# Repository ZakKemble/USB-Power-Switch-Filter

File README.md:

USB Power Switch and Filter
===========================

A simple USB power switch with current limit, soft start, noise filtering and ESD protection.

http://blog.zakkemble.co.uk/usb-power-switch-and-filter/

---

Zak Kemble

contact@zakkemble.co.uk

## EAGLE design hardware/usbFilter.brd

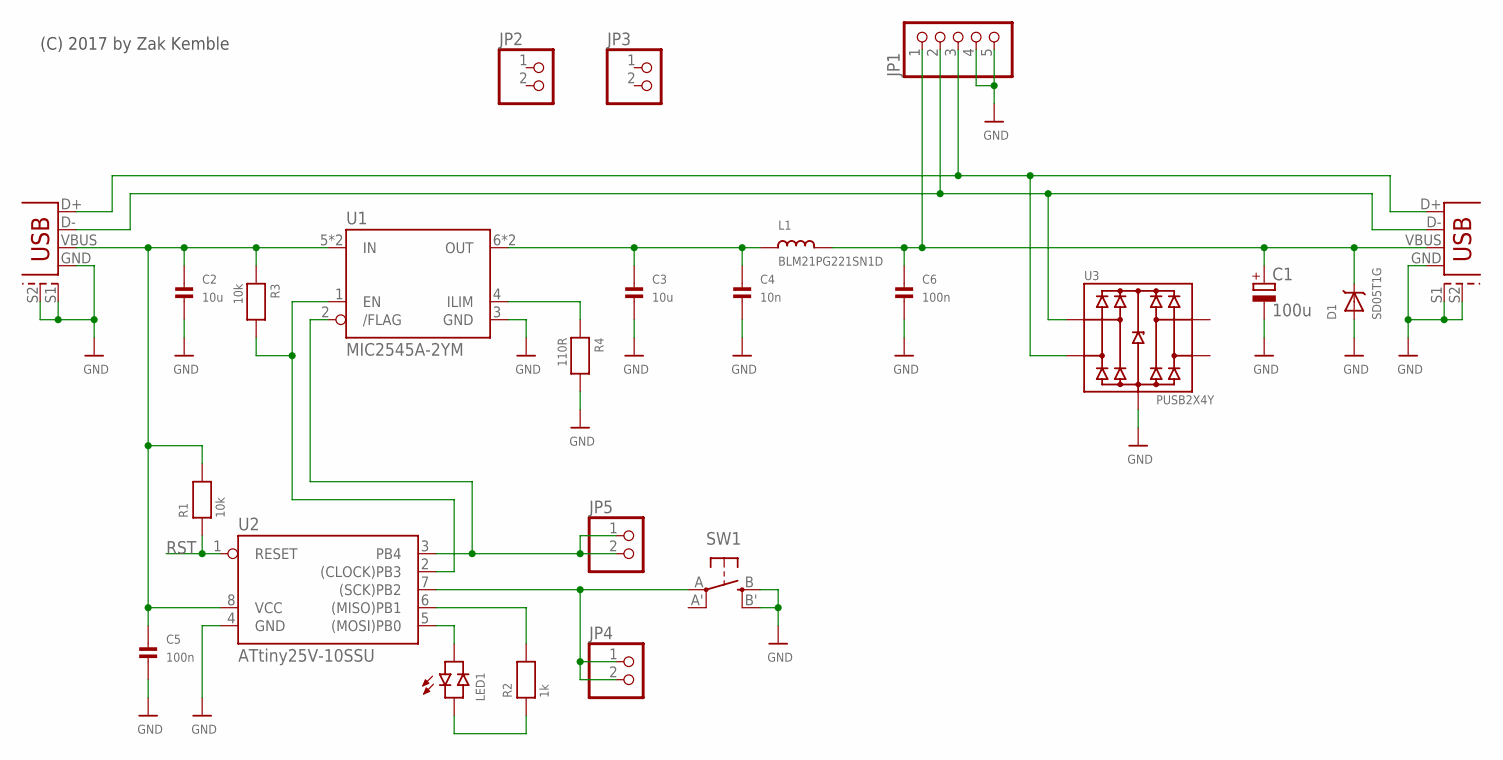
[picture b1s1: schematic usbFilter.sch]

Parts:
C1: 100u; E2,5-6
C2, C3: 10u; 0805_NO_OUTLINE
C4: 10n; 0402
C5, C6: 100n; 0402
D1: SD05T1G; SOD-323
JP1: PINHD-1X5; 1X05
JP2, JP3, JP4, JP5: PINHD-1X2; 1X02
L1: BLM21PG221SN1D; 0805_NO_OUTLINE
LED1: LEDBI0805; CHIPLED_0805_NOOUTLINE
R1, R3: 10k; 0402
R2: 1k; 0402
R4: 110R; 0805_NO_OUTLINE
SW1: SPST_TACTMC32882; TACT_SMD4
U1: MIC2545A-2YM; SOIC8_150MIL_SMPAD
U2: ATtiny25V-10SSU; SOIC8_150MIL_SMPAD
U3: PUSB2X4Y; SOT-363
USB1: USB-TYPE-B
USB2: USB-TYPE-A-VERT

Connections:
GND: C1.-, C2.2, C3.2, C4.2, C5.2, C6.2, D1.A, JP1.4, JP1.5, R4.2, SW1.B (S), SW1.B' (S1), U1.3 (GND), U2.4 (GND), U3.2 (GND), USB1.GND, USB1.S1 (SHEILD1), USB1.S2 (SHEILD2), USB2.GND, USB2.S1 (SHEILD1), USB2.S2 (SHEILD2)
unnamed: C2.1, C5.1, R1.2, R3.1, U1.5 (IN), U1.7 (IN), U2.8 (VCC), USB1.VBUS
unnamed: JP1.2, U3.1 (IO1), USB1.D-, USB2.D-
unnamed: C3.1, C4.1, L1.1, U1.6 (OUT), U1.8 (OUT)
unnamed: JP1.3, U3.3 (IO2), USB1.D+, USB2.D+
unnamed: C1.+, C6.1, D1.C, JP1.1, L1.2, USB2.VBUS
unnamed: R3.2, U1.1 (EN), U2.2 ((CLOCK)PB3)
unnamed: JP5.1, JP5.2, U1.2 (/FLAG), U2.3 (PB4)
unnamed: R4.1, U1.4 (ILIM)
unnamed: LED1.C, R2.1
unnamed: R2.2, U2.6 ((MISO)PB1)
unnamed: LED1.A, U2.5 ((MOSI)PB0)
unnamed: JP4.1, JP4.2, SW1.A, U2.7 ((SCK)PB2)
RST: R1.1, U2.1 (RESET)

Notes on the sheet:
(C) 2017 by Zak Kemble

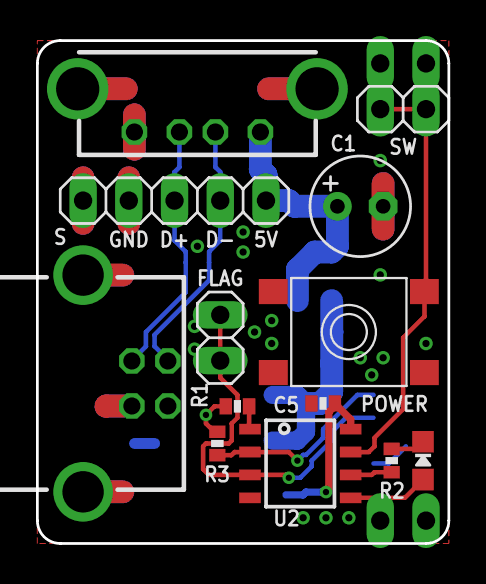
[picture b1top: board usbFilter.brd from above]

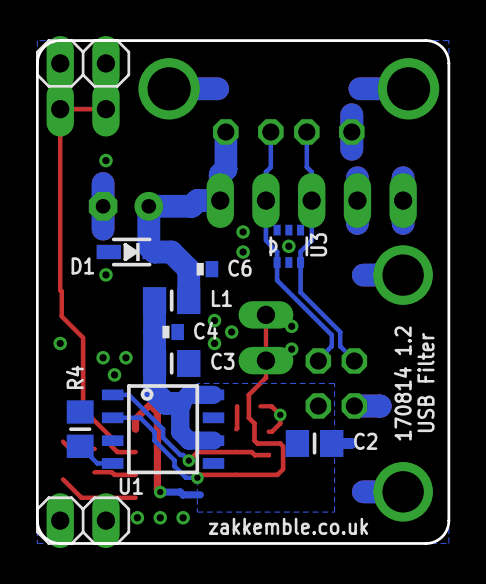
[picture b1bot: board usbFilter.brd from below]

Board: 2 copper layers, 22.9 x 27.9 mm, 24 parts (11 on the bottom side), 14 nets.

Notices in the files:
parts and their libraries:
microbuilder: This work is placed in the public domain, and may be freely used for commercial and non-commercial work with the following conditions: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
